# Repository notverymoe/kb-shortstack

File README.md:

# Shortstop

This is a weird small olkb with knob.

# License

Copyright 2024, Natalie Baker

GPLv3.0 or Later. See LICENSE.md for full text, or:
https://www.gnu.org/licenses/gpl-3.0.en.html

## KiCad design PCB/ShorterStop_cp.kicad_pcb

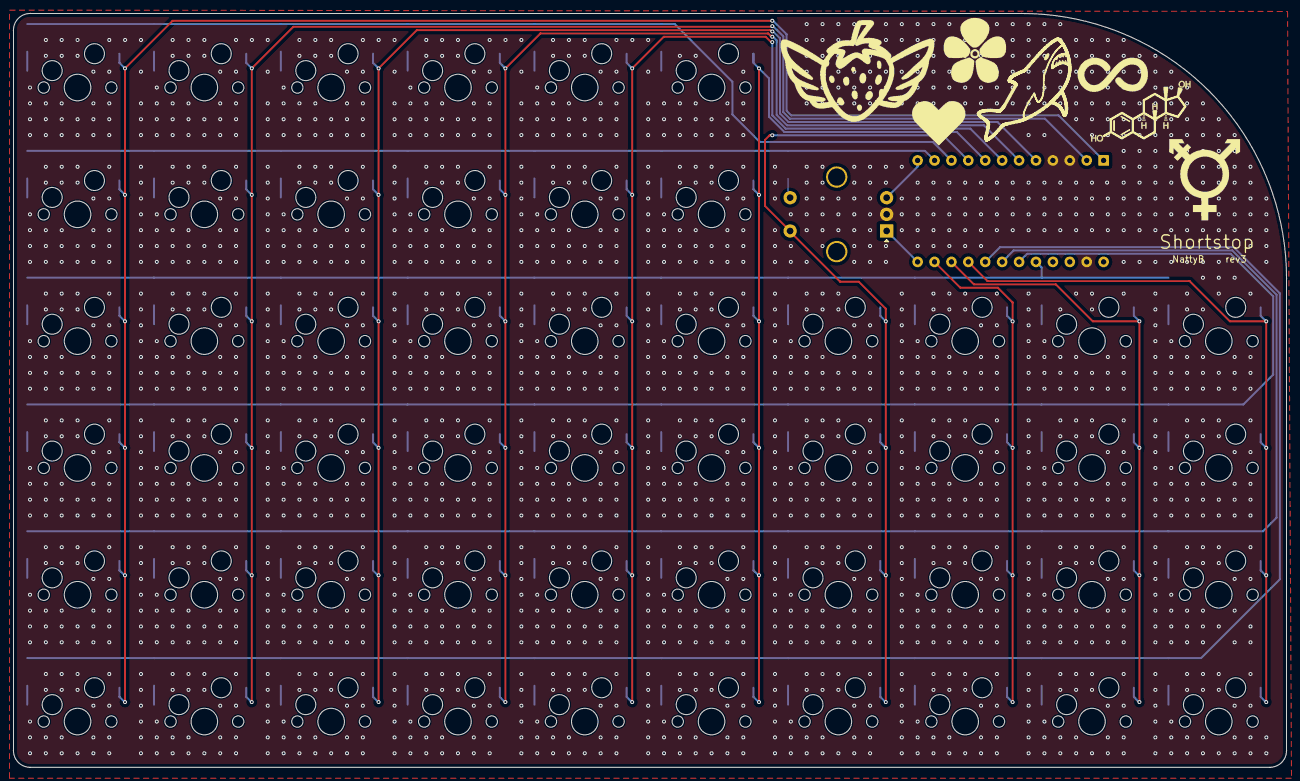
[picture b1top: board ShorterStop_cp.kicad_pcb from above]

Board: 2 copper layers, 191.2 x 113.2 mm, 53 parts (0 on the bottom side), 10 nets.

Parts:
R01-C01, R01-C02, R01-C03, R01-C04, R01-C05, R01-C06, R02-C01, R02-C02, R02-C03, R02-C04, R02-C05, R02-C06, R03-C01, R03-C02, R03-C03, R03-C04, R03-C05, R03-C06, R03-C07, R03-C08, R03-C09, R03-C10, R04-C01, R04-C02, R04-C03, R04-C04, R04-C05, R04-C06, R04-C07, R04-C08, R04-C09, R04-C10, R05-C01, R05-C02, R05-C03, R05-C04, R05-C05, R05-C06, R05-C07, R05-C08, R05-C09, R05-C10, R06-C01, R06-C02, R06-C03, R06-C04, R06-C05, R06-C06, R06-C07, R06-C08, R06-C09, R06-C10: Kailh_socket_MX_NoMountSilk
RotaryEncoder: RotaryEncoder_Alps_EC11E-Switch_Vertical_H20mm_Ci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; RotaryEncoder_Alps_EC11E-Switch_Vertical_H20mm_CircularMoun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

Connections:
Col1: R01-C01.1, R02-C01.1, R03-C01.1, R04-C01.1, R05-C01.1, R06-C01.1
Col2: R01-C02.1, R02-C02.1, R03-C02.1, R04-C02.1, R05-C02.1, R06-C02.1
Col3: R01-C03.1, R02-C03.1, R03-C03.1, R04-C03.1, R05-C03.1, R06-C03.1
Col4: R01-C04.1, R02-C04.1, R03-C04.1, R04-C04.1, R05-C04.1, R06-C04.1
Col5: R01-C05.1, R02-C05.1, R03-C05.1, R04-C05.1, R05-C05.1, R06-C05.1
Col6: R01-C06.1, R02-C06.1, R03-C06.1, R04-C06.1, R05-C06.1, R06-C06.1
Col7: R03-C07.1, R04-C07.1, R05-C07.1, R06-C07.1, RotaryEncoder.S2
Col8: R03-C08.1, R04-C08.1, R05-C08.1, R06-C08.1
Col9: R03-C09.1, R04-C09.1, R05-C09.1, R06-C09.1
Col10: R03-C10.1, R04-C10.1, R05-C10.1, R06-C10.1
